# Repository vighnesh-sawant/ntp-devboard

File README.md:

# A devboard with a gps module and ethernet
This devboard will work as stratum 1 NTP server and has support for PTP also which I plan on supporting. Since this is my first hardware project I have picked simple(?) components  
It will take time from the gps module and serve it as a ptp/ntp server over the lan9250.

# Why
Mostly for fun but I WANT MY LAPTOP TO HAVE MORE ACCURATE TIME THAN MY FRIENDS.
I used to do this same thing with a phone but its accuracy was on the same level as ntp over the public internet  
Thats why I wanted my own STRATUM 1 Server at home, this is also a good project for learning a variety of different stuff ranging from pcb development to writing drivers to messing with ptp.

# How
Get this pcb printed, make sure to get a gps module with a PPS pin and connect the pins via breadboard / soldering   
to the gpio pins of the rp2040, then use my firmware and connect the ethernet cable to your pc.  
Make sure to change the gpio pins in the header to the ones you have connected.
Change your ntp server to point to the rp2040's ip and then done!  
You have your own stratum 1 ntp server  
More instrucions coming after I get my PCB printed!

# Schematic and stuff

# BOM TABLE

| JLCPCB BOM Tool - BOM Matching                                                                              |                   |                                  |                                             |               |                    |                   |                                                                                                                                                           |                |                                                                                                                                                                                                             |                                                            |                                                                                                                         |                   |                                                                          |          |     |           |                 |
| ----------------------------------------------------------------------------------------------------------- | ----------------- | -------------------------------- | ------------------------------------------- | ------------- | ------------------ | ----------------- | --------------------------------------------------------------------------------------------------------------------------------------------------------- | -------------- | ----------------------------------------------------------------------------------------------------------------------------------------------------------------------------------------------------------- | ---------------------------------------------------------- | ----------------------------------------------------------------------------------------------------------------------- | ----------------- | ------------------------------------------------------------------------ | -------- | --- | --------- | --------------- |
| BOM name：rev4_bom-JLCPCB Assembly Order.xlsx                                                                |                   |                                  | Download Time：2026-03-09 22:30:55           |               |                    |                   | * Our matching results are updated in real-time, but stock and prices may change. 
If it's been over 24 hours, please re-match before placing your order. |                |                                                                                                                                                                                                             |                                                            |                                                                                                                         |                   |                                                                          |          |     |           |                 |
| PCB Assembled Qty：5                                                                                         |                   |                                  | Est. Total Price：36.7342                    |               |                    |                   |                                                                                                                                                           |                |                                                                                                                                                                                                             |                                                            |                                                                                                                         |                   |                                                                          |          |     |           |                 |
| Your BOM                                                                                                    |                   |                                  |                                             |               | Matched Parts      |                   |                                                                                                                                                           |                |                                                                                                                                                                                                             |                                                            |                                                                                                                         | Order Information |                                                                          |          |     |           |                 |
| Top Designator                                                                                              | Bottom Designator | Comment                          | Footprint                                   | JLCPCB Part # | Matches            | Part #            | Manufacturer                                                                                                                                              | Footprint      | Description                                                                                                                                                                                                 | Category                                                   | Warning                                                                                                                 | JLCPCB Part #     | Product link                                                             | Lib Type | Qty | Source    | Total Price ($) |
| C1,C10,C23,C24                                                                                              |                   | 1uF                              | 0402                                        |               | Select by System   | CL05A105KA5NQNC   | Samsung Electro-Mechanics                                                                                                                                 | 0402           | 1uF 25V X5R ±10% 0402 Multilayer Ceramic Capacitors MLCC - SMD/SMT ROHS                                                                                                                                     | Multilayer Ceramic Capacitors MLCC - SMD/SMT               |                                                                                                                         | C52923            | https://jlcpcb.com/partdetail/53938-CL05A105KA5NQNC/C52923               | Basic    | 8   | 8 JLCPCB  | 0.032           |
| C11,C12,C17,C2,C20,C21,C22,C25,C26,C27,C28,C29,C3,C30,C31,C32,C33,C34,C35,C36,C38,C39,C4,C40,C5,C6,C7,C8,C9 |                   | 0.1uF                            | 0402                                        |               | Unconfirmed        | CL05B104KO5NNNC   | Samsung Electro-Mechanics                                                                                                                                 | 0402           | 100nF 16V X7R ±10% 0402 Multilayer Ceramic Capacitors MLCC - SMD/SMT ROHS                                                                                                                                   | Multilayer Ceramic Capacitors MLCC - SMD/SMT               | 1.The comment (CL05B104KO5NNNC) of this part does not match the one (0.1uF) provided in your BOM. Please confirm;       | C1525             | https://jlcpcb.com/partdetail/1877-CL05B104KO5NNNC/C1525                 | Basic    | 58  | 58 JLCPCB | 0.0754          |
| C13,C14                                                                                                     |                   | 10uF                             | 0603                                        |               | Select by System   | CL10A106KP8NNNC   | Samsung Electro-Mechanics                                                                                                                                 | 0603           | 10V 10uF X5R ±10% 0603 Multilayer Ceramic Capacitors MLCC - SMD/SMT ROHS                                                                                                                                    | Multilayer Ceramic Capacitors MLCC - SMD/SMT               |                                                                                                                         | C19702            | https://jlcpcb.com/partdetail/20411-CL10A106KP8NNNC/C19702               | Basic    | 4   | 4 JLCPCB  | 0.026           |
| C15,C16                                                                                                     |                   | 33pF                             | 0402                                        |               | Select by System   | 0402CG330J500NT   | FH (Guangdong Fenghua Advanced Tech)                                                                                                                      | 0402           | 33pF 50V C0G ±5% 0402 Multilayer Ceramic Capacitors MLCC - SMD/SMT ROHS                                                                                                                                     | Multilayer Ceramic Capacitors MLCC - SMD/SMT               |                                                                                                                         | C1562             | https://jlcpcb.com/partdetail/1914-0402CG330J500NT/C1562                 | Basic    | 4   | 4 JLCPCB  | 0.0048          |
| C18,C19                                                                                                     |                   | 15pF                             | 0402                                        |               | Select by System   | 0402CG150J500NT   | FH (Guangdong Fenghua Advanced Tech)                                                                                                                      | 0402           | 15pF 50V C0G ±5% 0402 Multilayer Ceramic Capacitors MLCC - SMD/SMT ROHS                                                                                                                                     | Multilayer Ceramic Capacitors MLCC - SMD/SMT               |                                                                                                                         | C1548             | https://jlcpcb.com/partdetail/1900-0402CG150J500NT/C1548                 | Basic    | 4   | 4 JLCPCB  | 0.0048          |
| C37                                                                                                         |                   | 470pF                            | 0805                                        |               | Select by System   | 0805B471K500NT    | FH (Guangdong Fenghua Advanced Tech)                                                                                                                      | 0805           | 470pF 50V X7R ±10% 0805 Multilayer Ceramic Capacitors MLCC - SMD/SMT ROHS                                                                                                                                   | Multilayer Ceramic Capacitors MLCC - SMD/SMT               |                                                                                                                         | C1743             | https://jlcpcb.com/partdetail/2095-0805B471K500NT/C1743                  | Basic    | 2   | 2 JLCPCB  | 0.0104          |
| FB1,FB2,FB3,FB4                                                                                             |                   | FerriteBead                      | 0603                                        |               | Select by Customer | GZ1608D601TF      | Sunlord                                                                                                                                                   | 0603           | -55℃~+125℃ 1 200mA 450mΩ 600Ω@100MHz ±25% 0603 Ferrite Beads ROHS                                                                                                                                           | Ferrite Beads                                              |                                                                                                                         | C1002             | https://jlcpcb.com/partdetail/Sunlord-GZ1608D601TF/C1002                 | Basic    | 8   | 8 JLCPCB  | 0.1048          |
| J1                                                                                                          |                   | USB_C_Receptacle_USB2.0_14P      | USB_C_Receptacle_HRO_TYPE-C-31-M-12         |               | Select by Customer | TYPE-C-31-M-12    | Korean Hroparts Elec                                                                                                                                      | SMD            | -30℃~+80℃ 1 10,000 cycles 16P 20V 5A 7.35mm Female Surface Mount, Right Angle Type-C SMD USB Connectors ROHS                                                                                                | USB Connectors                                             |                                                                                                                         | C165948           | https://jlcpcb.com/partdetail/Korean_HropartsElec-TYPE_C_31_M12/C165948  | Extended | 2   | 2 JLCPCB  | 0.362           |
| R1,R2                                                                                                       |                   | 5.1K                             | 0402                                        |               | Unconfirmed        | 0402WGF5101TCE    | UNI-ROYAL(Uniroyal Elec)                                                                                                                                  | 0402           | -55℃~+155℃ 5.1kΩ 50V 62.5mW Thick Film Resistor ±1% ±100ppm/℃ 0402 Chip Resistor - Surface Mount ROHS                                                                                                       | Chip Resistor - Surface Mount                              | 1.The comment (0402WGF5101TCE) of this part does not match the one (5.1K) provided in your BOM. Please confirm;         | C25905            | https://jlcpcb.com/partdetail/26648-0402WGF5101TCE/C25905                | Basic    | 4   | 4 JLCPCB  | 0.0032          |
| R3,R4                                                                                                       |                   | 22                               | 0402                                        |               | Unconfirmed        | 0402WGF220JTCE    | UNI-ROYAL(Uniroyal Elec)                                                                                                                                  | 0402           | -55℃~+155℃ 22Ω 50V 62.5mW Thick Film Resistor ±1% ±100ppm/℃ 0402 Chip Resistor - Surface Mount ROHS                                                                                                         | Chip Resistor - Surface Mount                              | 1.The comment (0402WGF220JTCE) of this part does not match the one (22) provided in your BOM. Please confirm;           | C25092            | https://jlcpcb.com/partdetail/25835-0402WGF220JTCE/C25092                | Basic    | 4   | 4 JLCPCB  | 0.0032          |
| R5,R6,R8                                                                                                    |                   | 1K                               | 0402                                        |               | Unconfirmed        | 0402WGF1001TCE    | UNI-ROYAL(Uniroyal Elec)                                                                                                                                  | 0402           | -55℃~+155℃ 1kΩ 50V 62.5mW Thick Film Resistor ±1% ±100ppm/℃ 0402 Chip Resistor - Surface Mount ROHS                                                                                                         | Chip Resistor - Surface Mount                              | 1.The comment (0402WGF1001TCE) of this part does not match the one (1K) provided in your BOM. Please confirm;           | C11702            | https://jlcpcb.com/partdetail/12256-0402WGF1001TCE/C11702                | Basic    | 6   | 6 JLCPCB  | 0.0042          |
| R10,R11,R12,R13,R16,R7,R9                                                                                   |                   | 10K                              | 0402                                        |               | Unconfirmed        | 0402WGF1002TCE    | UNI-ROYAL(Uniroyal Elec)                                                                                                                                  | 0402           | -55℃~+155℃ 10kΩ 50V 62.5mW Thick Film Resistor ±1% ±100ppm/℃ 0402 Chip Resistor - Surface Mount ROHS                                                                                                        | Chip Resistor - Surface Mount                              | 1.The comment (0402WGF1002TCE) of this part does not match the one (10K) provided in your BOM. Please confirm;          | C25744            | https://jlcpcb.com/partdetail/26487-0402WGF1002TCE/C25744                | Basic    | 14  | 14 JLCPCB | 0.0112          |
| R15                                                                                                         |                   | 12K                              | 0402                                        |               | Unconfirmed        | 0402WGF1202TCE    | UNI-ROYAL(Uniroyal Elec)                                                                                                                                  | 0402           | -55℃~+155℃ 12kΩ 50V 62.5mW Thick Film Resistor ±1% ±100ppm/℃ 0402 Chip Resistor - Surface Mount ROHS                                                                                                        | Chip Resistor - Surface Mount                              | 1.The comment (0402WGF1202TCE) of this part does not match the one (12K) provided in your BOM. Please confirm;          | C25752            | https://jlcpcb.com/partdetail/26495-0402WGF1202TCE/C25752                | Basic    | 2   | 2 JLCPCB  | 0.0014          |
| SW1                                                                                                         |                   | SW_Push                          | SW_Push_SPST_NO_Alps_SKRK                   |               | Select by Customer | TS-1088-AR02016   | XUNPU                                                                                                                                                     | SMD,4x3mm      | -30℃~+80℃ 1.6N 100,000 cycles 12V 2mm 3mm 4mm 50mA Black Round Button SMD(SMT) Tab SPST Surface Mount,Vertical Without Bracket SMD,4x3mm Tactile Switches ROHS                                              | Tactile Switches                                           |                                                                                                                         | C720477           | https://jlcpcb.com/partdetail/XUNPU-TS_1088AR02016/C720477               | Basic    | 2   | 2 JLCPCB  | 0.111           |
| U1                                                                                                          |                   | RP2040                           | QFN-56-1EP_7x7mm_P0.4mm_EP3.2x3.2mm         |               | Select by Customer | RP2040            | Raspberry Pi                                                                                                                                              | LQFN-56(7x7)   | 12bit 133MHz 30 LQFN-56(7x7) Microcontrollers (MCU/MPU/SOC) ROHS                                                                                                                                            | Microcontrollers (MCU/MPU/SOC)                             |                                                                                                                         | C2040             | https://jlcpcb.com/partdetail/RaspberryPi-RP2040/C2040                   | Extended | 2   | 2 JLCPCB  | 1.9298          |
| U2                                                                                                          |                   | MCP1700x-330xxTT                 | SOT-23                                      |               | Select by Customer | MCP1700T-3302E/TT | Microchip Tech                                                                                                                                            | SOT-23         | -40℃~+125℃@(Tj) 1 1.6uA 178mV@(250mA) 250mA 3.3V 44dB@(100Hz) 6V Fixed Over Temperature Protection、Short Circuit Protection Positive SOT-23 Voltage Regulators - Linear, Low Drop Out (LDO) Regulators ROHS | Voltage Regulators - Linear, Low Drop Out (LDO) Regulators |                                                                                                                         | C39051            | https://jlcpcb.com/partdetail/MicrochipTech-MCP1700T_3302ETT/C39051      | Extended | 5   | 5 JLCPCB  | 2.193           |
| U3                                                                                                          |                   | LAN9250/ML                       | QFN64_ML_MCH                                |               | Select by System   | LAN9250/ML        | Microchip Tech                                                                                                                                            | QFN-64-EP(9x9) | QFN-64-EP(9x9) Ethernet Controllers ROHS                                                                                                                                                                    | Ethernet Controllers                                       |                                                                                                                         | C633497           | https://jlcpcb.com/partdetail/MicrochipTech-LAN9250ML/C633497            | Extended | 2   | 2 JLCPCB  | 28.7744         |
| U4                                                                                                          |                   | W25Q16JVUXIQTR                   | Winbond_USON-8-1EP_3x2mm_P0.5mm_EP0.2x1.6mm |               | Select by Customer | W25Q16JVUXIQ      | Winbond Elec                                                                                                                                              | USON-8-EP(2x3) | -40℃~+85℃ 100,000 cycles 10uA 133MHz 16Mbit 2.7V~3.6V 20 Years 3ms SPI USON-8-EP(2x3) NOR FLASH ROHS                                                                                                        | NOR FLASH                                                  | 1.The comment (W25Q16JVUXIQ) of this part does not match the one (W25Q16JVUXIQTR) provided in your BOM. Please confirm; | C2843335          | https://jlcpcb.com/partdetail/WinbondElec-W25Q16JVUXIQ/C2843335          | Extended | 2   | 2 JLCPCB  | 2.792           |
| Y1                                                                                                          |                   | 12MHz                            | Crystal_SMD_3225-4Pin_3.2x2.5mm             |               | Select by Customer | X322512MSB4SI     | YXC Crystal Oscillators                                                                                                                                   | SMD3225-4P     | -40℃~+85℃ 12MHz 20pF Crystal Oscillator ±10ppm ±20ppm SMD3225-4P Crystals ROHS                                                                                                                              | Crystals                                                   |                                                                                                                         | C9002             | https://jlcpcb.com/partdetail/YXC_CrystalOscillators-X322512MSB4SI/C9002 | Basic    | 2   | 2 JLCPCB  | 0.145           |
| Y2                                                                                                          |                   | 25MHz                            | Crystal_SMD_3225-4Pin_3.2x2.5mm             |               | Select by Customer | X322525MOB4SI     | YXC Crystal Oscillators                                                                                                                                   | SMD3225-4P     | -40℃~+85℃ 12pF 25MHz Crystal Oscillator ±10ppm ±20ppm SMD3225-4P Crystals ROHS                                                                                                                              | Crystals                                                   |                                                                                                                         | C9006             | https://jlcpcb.com/partdetail/YXC_CrystalOscillators-X322525MOB4SI/C9006 | Basic    | 2   | 2 JLCPCB  | 0.1456          |
| J2                                                                                                          |                   | Conn_01x07                       | PinHeader_1x07_P2.54mm_Vertical             |               | No matches         | No Part Selected  |                                                                                                                                                           |                |                                                                                                                                                                                                             |                                                            |                                                                                                                         |                   |                                                                          |          |     |           |                 |
| J4                                                                                                          |                   | Conn_01x04                       | PinHeader_1x04_P2.54mm_Vertical             |               | No matches         | No Part Selected  |                                                                                                                                                           |                |                                                                                                                                                                                                             |                                                            |                                                                                                                         |                   |                                                                          |          |     |           |                 |
| J5                                                                                                          |                   | Conn_01x02                       | PinHeader_1x02_P2.54mm_Vertical             |               | No matches         | No Part Selected  |                                                                                                                                                           |                |                                                                                                                                                                                                             |                                                            |                                                                                                                         |                   |                                                                          |          |     |           |                 |
| J6                                                                                                          |                   | RJ45_Hanrun_HR911105A_Horizontal | RJ45_Hanrun_HR911105A_Horizontal            |               | No matches         | No Part Selected  |                                                                                                                                                           |                |                                                                                                                                                                                                             |                                                            |                                                                                                                         |                   |                                                                          |          |     |           |                 |
| ﻿Index | LCSC#    | MPN                   | Manufacturer                  | Package               | Customer # | Description                                                           | RoHS | Quantity | MOQ | Multiple | Unit Price($) | Extended Price($) | Product Link                                      |
| ------ | -------- | --------------------- | ----------------------------- | --------------------- | ---------- | --------------------------------------------------------------------- | ---- | -------- | --- | -------- | ------------- | ----------------- | ------------------------------------------------- |
| 1      | C12074   | HR911105A             | HANRUN(Zhongshan HanRun Elec) | Through Hole          |            | Jack Modular Connector RJ45 Through Hole                              | yes  | 2        | 1   | 1        | 1.4814        | 2.96              | https://www.lcsc.com/product-detail/C12074.html   |
| 2      | C2337    | 2.54-1*40P            | BOOMELE(Boom Precision Elec)  | Through Hole,P=2.54mm |            | Pin Header 40 Position 2.54mm Pitch Single Row Through Hole -25℃~+85℃ | yes  | 5        | 5   | 5        | 0.1372        | 0.69              | https://www.lcsc.com/product-detail/C2337.html    |
| 3      | C5139763 | HS13L01WZ01           | HS                            | -                     |            | 1.3 128x64 sh1106 SPI LCD, OLED, Graphic RoHS                         | yes  | 2        | 1   | 1        | 4.6311        | 9.26              | https://www.lcsc.com/product-detail/C5139763.html |
| 4      | C9753    | DS18B20+              | MAXIM                         | TO-92                 |            | -55℃~+125℃ Single-bus 3V~5.5V TO-92 Analog and Digital Output RoHS    | yes  | 1        | 1   | 1        | 1.1630        | 1.16              | https://www.lcsc.com/product-detail/C9753.html    |
| 5      | C784382  | BWGNSCNX18-18B1Y2L120 | BAT WIRELESS                  | -                     |            | RF ANTENNA Ceramic                                                    | yes  | 1        | 1   | 1        | 1.6729        | 1.67              | https://www.lcsc.com/product-detail/C784382.html  |

A Gps module with a PPS pin https://roboticsdna.in/product/gps-neo-6m-satellite-positioning-module-development-board-for-arduino-stm32-51/  
Jumper wire https://roboticsdna.in/product/65pcs-flexible-breadboard-jumper-wires/  
Bread Board https://roboticsdna.in/product/syb-170-black-mini-solderless-breadboard/

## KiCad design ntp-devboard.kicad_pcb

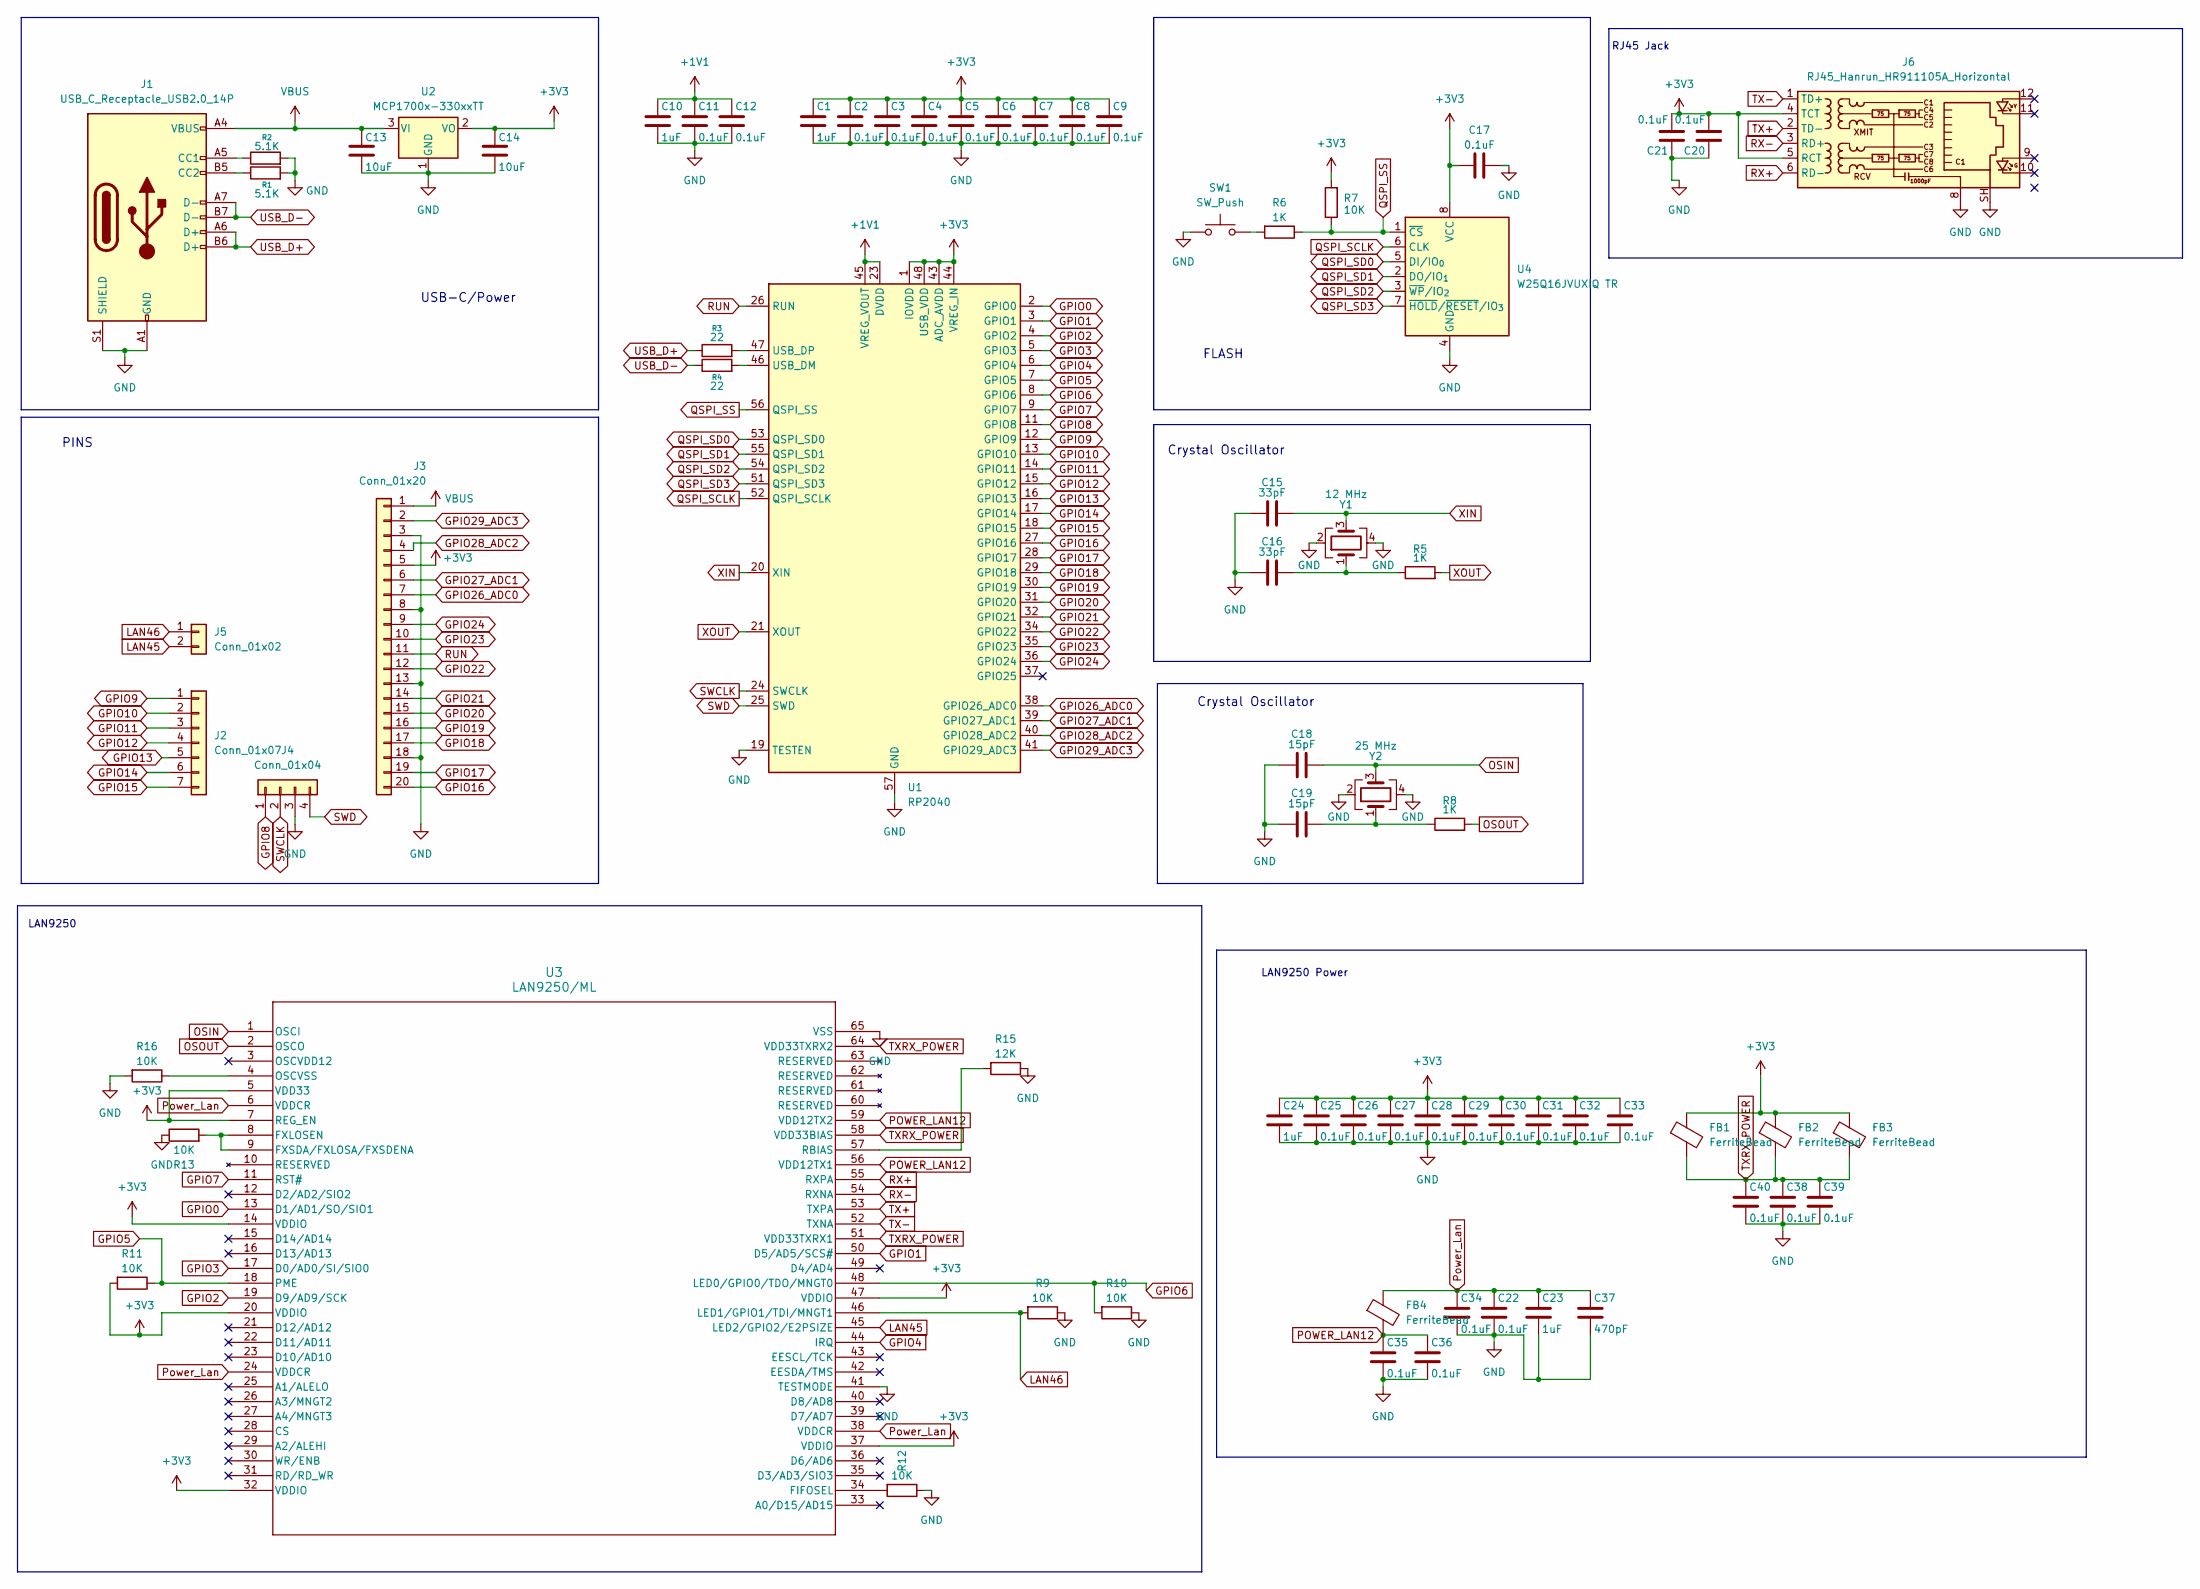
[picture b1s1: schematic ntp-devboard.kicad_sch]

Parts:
C1, C10, C23, C24: 1uF; C_0402_1005Metric
C2, C3, C4, C5, C6, C7, C8, C9, C11, C12, C17, C20, C21, C22, C25, C26, C27, C28, C29, C30, C31, C32, C33, C34, C35, C36, C38, C39, C40: 0.1uF; C_0402_1005Metric
C13, C14: 10uF; C_0603_1608Metric
C15, C16: 33pF; C_0402_1005Metric
C18, C19: 15pF; C_0402_1005Metric
C37: 470pF; C_0805_2012Metric
FB1, FB2, FB3, FB4: FerriteBead; L_0603_1608Metric
J1: USB_C_Receptacle_USB2.0_14P; USB_C_Receptacle_HRO_TYPE-C-31-M-12
J2: Conn_01x07; PinHeader_1x07_P2.54mm_Vertical
J3: Conn_01x20; PinHeader_1x20_P2.54mm_Vertical
J4: Conn_01x04; PinHeader_1x04_P2.54mm_Vertical
J5: Conn_01x02; PinHeader_1x02_P2.54mm_Vertical
J6: RJ45_Hanrun_HR911105A_Horizontal
R1, R2: 5.1K; R_0402_1005Metric
R3, R4: 22; R_0402_1005Metric
R5, R6, R8: 1K; R_0402_1005Metric
R7, R9, R10, R11, R12, R13, R16: 10K; R_0402_1005Metric
R15: 12K; R_0402_1005Metric
SW1: SW_Push; SW_Push_SPST_NO_Alps_SKRK
U1: RP2040; QFN-56-1EP_7x7mm_P0.4mm_EP3.2x3.2mm
U2: MCP1700x-330xxTT; SOT-23
U3: LAN9250/ML; QFN64_ML_MCH
U4: W25Q16JVUXIQ TR; Winbond_USON-8-1EP_3x2mm_P0.5mm_EP0.2x1.6mm
Y1: 12 MHz; Crystal_SMD_3225-4Pin_3.2x2.5mm
Y2: 25 MHz; Crystal_SMD_3225-4Pin_3.2x2.5mm

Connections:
+1V1: C10.1, C11.1, C12.1, U1.23 (DVDD), U1.45 (VREG_VOUT), U1.50 (DVDD)
+3V3: C1.1, C2.1, C3.1, C4.1, C5.1, C6.1, C7.1, C8.1, C9.1, C14.1, C17.1, C20.2, C21.2, C24.1, C25.1, C26.1, C27.1, C28.1, C29.1, C30.1, C31.1, C32.1, C33.1, FB1.1, FB2.1, FB3.1, J3.5, J6.4 (TCT), J6.5 (RCT), R7.2, R11.2, U1.1 (IOVDD), U1.10 (IOVDD), U1.22 (IOVDD), U1.33 (IOVDD), U1.42 (IOVDD), U1.43 (ADC_AVDD), U1.44 (VREG_IN), U1.48 (USB_VDD), U1.49 (IOVDD), U2.2 (VO), U3.5 (VDD33), U3.7 (REG_EN), U3.14 (VDDIO), U3.20 (VDDIO), U3.32 (VDDIO), U3.37 (VDDIO), U3.47 (VDDIO), U4.8 (VCC)
GND: C1.2, C2.2, C3.2, C4.2, C5.2, C6.2, C7.2, C8.2, C9.2, C10.2, C11.2, C12.2, C13.2, C14.2, C15.1, C16.1, C17.2, C18.1, C19.1, C20.1, C21.1, C22.2, C23.2, C24.2, C25.2, C26.2, C27.2, C28.2, C29.2, C30.2, C31.2, C32.2, C33.2, C34.2, C35.2, C36.2, C37.2, C38.2, C39.2, C40.2, J1.A1 (GND), J1.A12 (GND), J1.B1 (GND), J1.B12 (GND), J1.S1 (SHIELD), J3.3, J3.8, J3.13, J3.18, J4.3, J6.8, J6.SH, R1.2, R2.2, R9.1, R10.1, R12.1, R13.1, R15.1, R16.2, SW1.1, U1.19 (TESTEN), U1.57 (GND), U2.1 (GND), U3.41 (TESTMODE), U3.65 (VSS), U4.4 (GND), Y1.2, Y1.4, Y2.2, Y2.4
GPIO0: U1.2 (GPIO0), U3.13 (D1/AD1/SO/SIO1)
GPIO1: U1.3 (GPIO1), U3.50 (D5/AD5/SCS#)
GPIO2: U1.4 (GPIO2), U3.19 (D9/AD9/SCK)
GPIO3: U1.5 (GPIO3), U3.17 (D0/AD0/SI/SIO0)
GPIO4: U1.6 (GPIO4), U3.44 (IRQ)
GPIO5: R11.1, U1.7 (GPIO5), U3.18 (PME)
GPIO6: R10.2, U1.8 (GPIO6), U3.48 (LED0/GPIO0/TDO/MNGT0)
GPIO7: U1.9 (GPIO7), U3.11 (RST#)
GPIO8: J4.1, U1.11 (GPIO8)
GPIO9: J2.1, U1.12 (GPIO9)
GPIO10: J2.2, U1.13 (GPIO10)
GPIO11: J2.3, U1.14 (GPIO11)
GPIO12: J2.4, U1.15 (GPIO12)
GPIO13: J2.5, U1.16 (GPIO13)
GPIO14: J2.6, U1.17 (GPIO14)
GPIO15: J2.7, U1.18 (GPIO15)
GPIO16: J3.20, U1.27 (GPIO16)
GPIO17: J3.19, U1.28 (GPIO17)
GPIO18: J3.17, U1.29 (GPIO18)
GPIO19: J3.16, U1.30 (GPIO19)
GPIO20: J3.15, U1.31 (GPIO20)
GPIO21: J3.14, U1.32 (GPIO21)
GPIO22: J3.12, U1.34 (GPIO22)
GPIO23: J3.10, U1.35 (GPIO23)
GPIO24: J3.9, U1.36 (GPIO24)
GPIO26_ADC0: J3.7, U1.38 (GPIO26_ADC0)
GPIO27_ADC1: J3.6, U1.39 (GPIO27_ADC1)
GPIO28_ADC2: J3.4, U1.40 (GPIO28_ADC2)
GPIO29_ADC3: J3.2, U1.41 (GPIO29_ADC3)
LAN45: J5.2, U3.45 (LED2/GPIO2/E2PSIZE)
LAN46: J5.1, R9.2, U3.46 (LED1/GPIO1/TDI/MNGT1)
unnamed: C16.2, R5.1, Y1.1
unnamed: C19.2, R8.1, Y2.1
unnamed: J1.A5 (CC1), R2.1
unnamed: J1.B5 (CC2), R1.1
unnamed: R6.2, SW1.2
unnamed: R4.2, U1.46 (USB_DM)
unnamed: R3.2, U1.47 (USB_DP)
unnamed: R12.2, U3.34 (FIFOSEL)
unnamed: R13.2, U3.8 (FXLOSEN), U3.9 (FXSDA/FXLOSA/FXSDENA)
unnamed: R16.1, U3.4 (OSCVSS)
unnamed: R15.2, U3.57 (RBIAS)
OSIN: C18.2, U3.1 (OSCI), Y2.3
OSOUT: R8.2, U3.2 (OSCO)
POWER_LAN12: C35.1, C36.1, FB4.2, U3.56 (VDD12TX1), U3.59 (VDD12TX2)
Power_Lan: C22.1, C23.1, C34.1, C37.1, FB4.1, U3.6 (VDDCR), U3.24 (VDDCR), U3.38 (VDDCR)
QSPI_SCLK: U1.52 (QSPI_SCLK), U4.6 (CLK)
QSPI_SD0: U1.53 (QSPI_SD0), U4.5 (DI/IO_{0})
QSPI_SD1: U1.55 (QSPI_SD1), U4.2 (DO/IO_{1})
QSPI_SD2: U1.54 (QSPI_SD2), U4.3 (~WP/IO_{2})
QSPI_SD3: U1.51 (QSPI_SD3), U4.7 (~HOLD/~RESET/IO_{3})
QSPI_SS: R6.1, R7.1, U1.56 (QSPI_SS), U4.1 (~CS)
RUN: J3.11, U1.26 (RUN)
RX+: J6.6 (RD-), U3.55 (RXPA)
RX-: J6.3 (RD+), U3.54 (RXNA)
SWCLK: J4.2, U1.24 (SWCLK)
SWD: J4.4, U1.25 (SWD)
TX+: J6.2 (TD-), U3.53 (TXPA)
TX-: J6.1 (TD+), U3.52 (TXNA)
TXRX_POWER: C38.1, C39.1, C40.1, FB1.2, FB2.2, FB3.2, U3.51 (VDD33TXRX1), U3.58 (VDD33BIAS), U3.64 (VDD33TXRX2)
USB_D+: J1.A6 (D+), J1.B6 (D+), R3.1
USB_D-: J1.A7 (D-), J1.B7 (D-), R4.1
VBUS: C13.1, J1.A4 (VBUS), J1.A9 (VBUS), J1.B4 (VBUS), J1.B9 (VBUS), J3.1, U2.3 (VI)
XIN: C15.2, U1.20 (XIN), Y1.3
XOUT: R5.2, U1.21 (XOUT)

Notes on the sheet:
FLASH
PINS
LAN9250 Power
RJ45 Jack
LAN9250
Crystal Oscillator
USB-C/Power

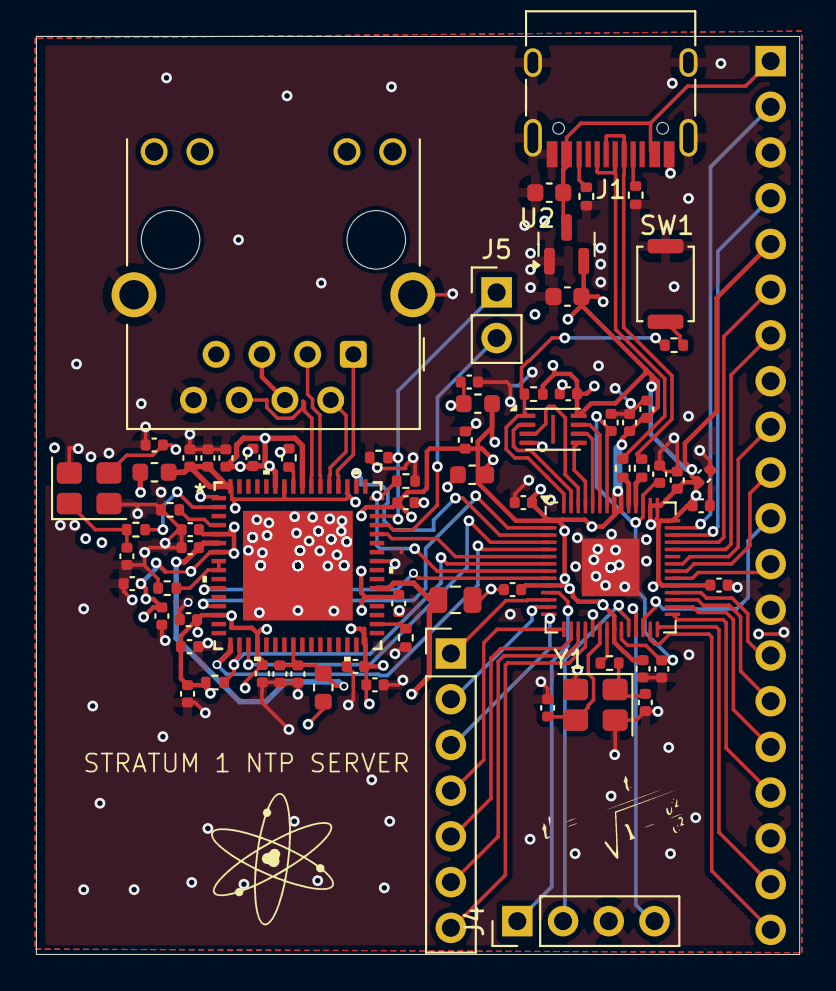
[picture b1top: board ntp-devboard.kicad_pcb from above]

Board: 4 copper layers, 42.4 x 51.0 mm, 72 parts (1 on the bottom side), 68 nets.

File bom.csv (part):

JLCPCB BOM Tool - BOM Matching,,,,,,,,,,,,,,,,,
BOM name：ntp-devboard(5)-JLCPCB Assembly Order.xlsx,,,Download Time：2026-01-26 02:29:52,,,,"* Our matching results are updated in real-time, but stock and prices may change. 
If it's been over 24 hours, please re-match before placing your order.",,,,,,,,,,
PCB Assembled Qty：5,,,Est. Total Price：93.3442,,,,,,,,,,,,,,
Your BOM,,,,,Matched Parts,,,,,,,Order Information,,,,,
Top Designator,Bottom Designator,Comment,Footprint,JLCPCB Part #,Matches,Part # ,Manufacturer,Footprint,Description,Category,Warning,JLCPCB Part #,Product link,Lib Type,Qty,Source,Total Price ($)
"C1,C10,C23,C24",,1uF,C_0402_1005Metric,,Select by Customer,CL05A105KA5NQNC,Samsung Electro-Mechanics,0402,1uF 25V X5R ±10% 0402 Multilayer Ceramic Capacitors MLCC - SMD/SMT ROHS,Multilayer Ceramic Capacitors MLCC - SMD/SMT,,C52923,https://jlcpcb.com/partdetail/53938-CL05A105KA5NQNC/C52923,Basic,20,20 JLCPCB,0.064
"C6,C5,C4,C2,C33,C20,C7,C29,C11,C36,C38,C35,C27,C9,C32,C40,C31,C12,C30,C8,C34,C17,C25,C22,C21,C3,C26,C39,C28",,0.1uF,C_0402_1005Metric,,Select by Customer,CL05B104KO5NNNC,Samsung Electro-Mechanics,0402,100nF 16V X7R ±10% 0402 Multilayer Ceramic Capacitors MLCC - SMD/SMT ROHS,Multilayer Ceramic Capacitors MLCC - SMD/SMT,1.The comment (CL05B104KO5NNNC) of this part does not match the one (0.1uF) provided in your BOM. Please confirm;,C1525,https://jlcpcb.com/partdetail/1877-CL05B104KO5NNNC/C1525,Basic,145,145 JLCPCB,0.1885
"C13,C14",,10uF,C_0603_1608Metric,,Select by Customer,CL10A106KP8NNNC,Samsung Electro-Mechanics,0603,10V 10uF X5R ±10% 0603 Multilayer Ceramic Capacitors MLCC - SMD/SMT ROHS,Multilayer Ceramic Capacitors MLCC - SMD/SMT,,C19702,https://jlcpcb.com/partdetail/20411-CL10A106KP8NNNC/C19702,Basic,10,10 JLCPCB,0.065
"C19,C15,C18,C16",,33pF,C_0402_1005Metric,,Select by Customer,0402CG330J500NT,FH (Guangdong Fenghua Advanced Tech),0402,33pF 50V C0G ±5% 0402 Multilayer Ceramic Capacitors MLCC - SMD/SMT ROHS,Multilayer Ceramic Capacitors MLCC - SMD/SMT,,C1562,https://jlcpcb.com/partdetail/1914-0402CG330J500NT/C1562,Basic,20,20 JLCPCB,0.022
C37,,470pF,C_0805_2012Metric,,Select by System,0805B471K500NT,FH (Guangdong Fenghua Advanced Tech),0805,470pF 50V X7R ±10% 0805 Multilayer Ceramic Capacitors MLCC - SMD/SMT ROHS,Multilayer Ceramic Capacitors MLCC - SMD/SMT,,C1743,https://jlcpcb.com/partdetail/2095-0805B471K500NT/C1743,Basic,5,5 JLCPCB,0.024
"FB2,FB3,FB1,FB4",,FerriteBead,L_0603_1608Metric,,Select by Customer,GZ1608D601TF,Sunlord,0603,-55℃~+125℃ 1 200mA 450mΩ 600Ω@100MHz ±25% 0603 Ferrite Beads ROHS,Ferrite Beads,,C1002,https://jlcpcb.com/partdetail/Sunlord-GZ1608D601TF/C1002,Basic,20,20 JLCPCB,0.244
J1,,USB_C_Receptacle_USB2.0_14P,USB_C_Receptacle_HRO_TYPE-C-31-M-12,,Select by Customer,TYPE-C-31-M-12,Korean Hroparts Elec,SMD,"-30℃~+80℃ 1 10,000 cycles 16P 20V 5A 7.35mm Female Surface Mount, Right Angle Type-C SMD USB Connectors ROHS",USB Connectors,,C165948,https://jlcpcb.com/partdetail/Korean_HropartsElec-TYPE_C_31_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,Extended,5,5 JLCPCB,0.886
J2,,Conn_01x07,PinHeader_1x07_P2.54mm_Vertical,,Select by Customer,2.54-1*40,ZHOURI,"插件,P=2.54mm","-40℃~+105℃ 1 1x40P 2.54mm 2.54mm 2.5A 3mm 40P 6mm Black Pin Header Through Hole Plugin,P=2.54mm Pin Headers ROHS",Pin Headers,,C2977586,https://jlcpcb.com/partdetail/ZHOURI-2_54_140/C2977586,Extended,0,0 JLCPCB,0
J4,,Conn_01x04,PinHeader_1x04_P2.54mm_Vertical,,Select by Customer,2.54-1*40P正弯针,BOOMELE(Boom Precision Elec),"弯插,P=2.54mm","-55℃~+105℃ 1 1x40P 2.54mm 2.54mm 3A 3mm 40P Black Brass Gold Pin Header Right Angle Push-Pull,P=2.54mm Pin Headers ROHS",Pin Headers,,C2334,https://jlcpcb.com/partdetail/2708-2_54_1_40P/C2334,Extended,0,0 JLCPCB,0
J6,,RJ45_Hanrun_HR911105A_Horizontal,RJ45_Hanrun_HR911105A_Horizontal,,Select by Customer,HR911105A,HANRUN(Zhongshan HanRun Elec),插件,0℃~+70℃ 1 Filtered Gold Non-PoE Phosphor bronze RJ45 Jack Right Angle Shielded With LED Plugin Ethernet Connectors / Modular Connectors (RJ45 RJ11) ROHS,Ethernet Connectors / Modular Connectors (RJ45 RJ11),,C12074,https://jlcpcb.com/partdetail/12651-HR911105A/C12074,Extended,5,5 JLCPCB,7.312
"R2,R1",,5.1K,R_0402_1005Metric,,Select by Customer,0402WGF5101TCE,UNI-ROYAL(Uniroyal Elec),0402,-55℃~+155℃ 5.1kΩ 50V 62.5mW Thick Film Resistor ±1% ±100ppm/℃ 0402 Chip Resistor - Surface Mount ROHS,Chip Resistor - Surface Mount,,C25905,https://jlcpcb.com/partdetail/26648-0402WGF5101TCE/C25905,Basic,10,10 JLCPCB,0.006
"R3,R4",,27,R_0402_1005Metric,,Select by Customer,0402WGF270JTCE,UNI-ROYAL(Uniroyal Elec),0402,-55℃~+155℃ 27Ω 50V 62.5mW Thick Film Resistor ±1% ±100ppm/℃ 0402 Chip Resistor - Surface Mount ROHS,Chip Resistor - Surface Mount,1.The comment (0402WGF270JTCE) of this part does not match the one (27) provided in your BOM. Please confirm;,C25100,https://jlcpcb.com/partdetail/25843-0402WGF270JTCE/C25100,Extended,22,22 JLCPCB,0.0132
"R8,R6,R5",,1K,R_0402_1005Metric,,Select by Customer,0402WGF1001TCE,UNI-ROYAL(Uniroyal Elec),0402,-55℃~+155℃ 1kΩ 50V 62.5mW Thick Film Resistor ±1% ±100ppm/℃ 0402 Chip Resistor - Surface Mount ROHS,Chip Resistor - Surface Mount,1.The comment (0402WGF1001TCE) of this part does not match the one (1K) provided in your BOM. Please confirm;,C11702,https://jlcpcb.com/partdetail/12256-0402WGF1001TCE/C11702,Basic,15,15 JLCPCB,0.009
"R10,R12,R7,R13,R9,R11,R16",,10K,R_0402_1005Metric,,Select by Customer,0402WGF1002TCE,UNI-ROYAL(Uniroyal Elec),0402,-55℃~+155℃ 10kΩ 50V 62.5mW Thick Film Resistor ±1% ±100ppm/℃ 0402 Chip Resistor - Surface Mount ROHS,Chip Resistor - Surface Mount,1.The comment (0402WGF1002TCE) of this part does not match the one (10K) provided in your BOM. Please confirm;,C25744,https://jlcpcb.com/partdetail/26487-0402WGF1002TCE/C25744,Basic,35,35 JLCPCB,0.0245
R15,,12.1K,R_0402_1005Metric,,Select by Customer,0402WGF1212TCE,UNI-ROYAL(Uniroyal Elec),0402,-55℃~+155℃ 12.1kΩ 50V 62.5mW Thick Film Resistor ±1% ±100ppm/℃ 0402 Chip Resistor - Surface Mount ROHS,Chip Resistor - Surface Mount,1.The comment (0402WGF1212TCE) of this part does not match the one (12.1K) provided in your BOM. Please confirm;,C25852,https://jlcpcb.com/partdetail/26595-0402WGF1212TCE/C25852,Extended,20,20 JLCPCB,0.012
SW1,,SW_Push,SW_Push_SPST_NO_Alps_SKRK,,Select by Customer,TS-1088-AR02016,XUNPU,"SMD,4x3mm","-30℃~+80℃ 1.6N 100,000 Cycles 12V 2mm 3mm 4mm 50mA Black Round Button SMD(SMT) Tab SPST Surface Mount,Vertical Without Bracket SMD,4x3mm Tactile Switches ROHS",Tactile Switches,,C720477,https://jlcpcb.com/partdetail/XUNPU-TS_1088AR02016/C720477,Basic,5,5 JLCPCB,0.222
U1,,RP2040,QFN-56-1EP_7x7mm_P0.4mm_EP3.2x3.2mm,,Select by Customer,RP2040,Raspberry Pi,LQFN-56(7x7),12bit 133MHz 30 LQFN-56(7x7) Microcontrollers (MCU/MPU/SOC) ROHS,Microcontrollers (MCU/MPU/SOC),,C2040,https://jlcpcb.com/partdetail/RaspberryPi-RP2040/C2040,Extended,5,5 JLCPCB,4.7885
U2,,MCP1700x-330xxTT,SOT-23,,Select by Customer,MCP1700T-3302E/TT,Microchip Tech,SOT-23,"-40℃~+125℃@(Tj) 1 1.6uA 178mV@(250mA) 250mA 3.3V 44dB@(100Hz) 6V Fixed Over Temperature Protection、Short Circuit Protection Positive SOT-23 Voltage Regulators - Linear, Low Drop Out (LDO) Regulators ROHS","Voltage Regulators - Linear, Low Drop Out (LDO) Regulators",,C39051,https://jlcpcb.com/partdetail/MicrochipTech-MCP1700T_3302ETT/C39051,Extended,5,5 JLCPCB,1.7915
U3,,LAN9250/ML,QFN64_ML_MCH,,Select by Customer,LAN9250/ML,Microchip Tech,QFN-64-EP(9x9),QFN-64-EP(9x9) Ethernet Controllers ROHS,Ethernet Controllers,,C633497,https://jlcpcb.com/partdetail/MicrochipTech-LAN9250ML/C633497,Extended,5,5 JLCPCB,71.401
U4,,W25Q16JVUXIQTR,Winbond_USON-8-1EP_3x2mm_P0.5mm_EP0.2x1.6mm,,Select by Customer,W25Q16JVUXIQ,Winbond Elec,USON-8-EP(2x3),"-40℃~+85℃ 100,000 Cycles 10uA 133MHz 16Mbit 2.7V~3.6V 20 Years 3ms SPI USON-8-EP(2x3) NOR FLASH ROHS",NOR FLASH,1.The comment (W25Q16JVUXIQ) of this part does not match the one (W25Q16JVUXIQTR) provided in your BOM. Please confirm;,C2843335,https://jlcpcb.com/partdetail/WinbondElec-W25Q16JVUXIQ/C2843335,Extended,5,5 JLCPCB,5.588
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
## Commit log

2026-01-21 Add production files
2026-01-21 bom optimisation
2026-01-21 verrrry basic firmware files
2026-01-25 add bom
2026-02-03 add 3d model
2026-02-03 uhm, _minor_ mistake
2026-02-04 cooked ah decoupling caps
2026-02-04 powertraces go brr
2026-02-04 add prod files
2026-02-04 umm?
2026-02-12 add lcsc.csv
2026-02-18 remove old prod files
2026-02-18 change xls to csv
2026-02-24 Improved schematic readbility
2026-03-09 update sch and pcb
2026-03-09 update bom
